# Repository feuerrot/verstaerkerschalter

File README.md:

# Verstärkerschalter

Dieses Projekt dient dazu, auf der Basis von
[vusb](http://www.obdev.at/vusb/) und
[powerswitch](http://www.obdev.at/products/vusb/powerswitch.html) die
Verstärker im [chaosdorf](https://www.chaosdorf.de) zu schalten.

Zudem hat die Platine bereits Bauteile für einen Anschluss per CAN-Bus, was
es später ermöglichen soll, die Platine an das geplante Bussystem im
Chaosdorf anzuschließen.

## Layout und so

### Schaltplan

### Layout

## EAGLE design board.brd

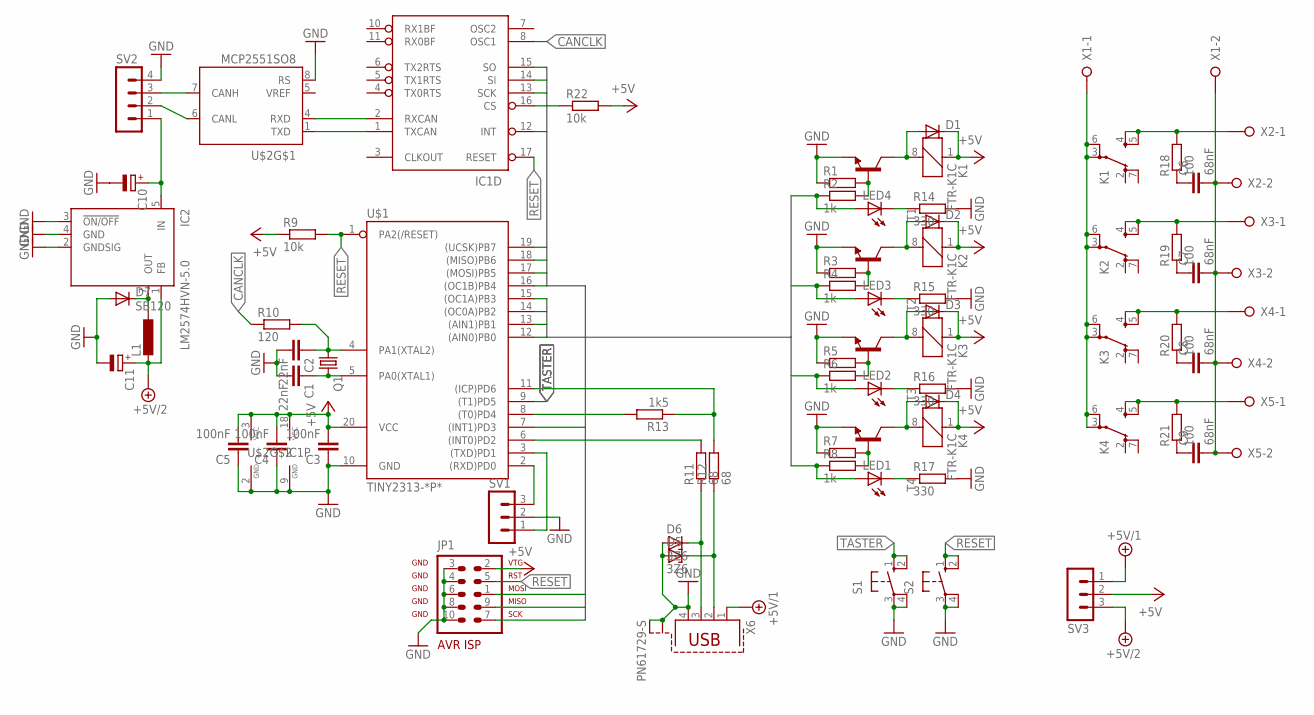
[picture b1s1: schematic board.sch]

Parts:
C1, C2: 22nF; C0805
C3, C4, C5: 100nF; C0805
C6, C7, C8, C9: 68nF; C150-084X183
C10, C11: CPOL-EUD; PANASONIC_D
D1, D2, D3, D4: DIODE-DO-214AC; DO-214AC
D5, D6: 3Z6; SMB
D7: SB120; DO41-10
IC1: MCP2515SO; SO-18W
IC2: LM2574HVN-5.0; DIL08
JP1: AVR-ISP-10
K1, K2, K3, K4: FTR-K1C
L1: L-EUPIS2816; PIS2816
LED1, LED2, LED3, LED4: LED5MM
Q1: CRYSTALHC49U70; HC49U70
R1, R3, R5, R7: R-EU_M0805; M0805
R2, R4, R6, R8: 1k; M0805
R9, R22: 10k; M0805
R10: 120; M0805
R11, R12: 68; M0805
R13: 1k5; M0805
R14, R15, R16, R17: 330; M0805
R18, R19, R20, R21: 100; P0613/15
S1, S2: 10-XX; B3F-10XX
SV1, SV3: MA03-1
SV2: MA04-1
T1, T2, T3, T4: -NPN-SOT23-EBC; SOT23-EBC
U$1: TINY2313-*P*; DIL20
U$2: MCP2551SO8; SO08
X1, X2, X3, X4, X5: W237-02P; W237-132
X6: PN61729-S

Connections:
+5V: C3.2, C4.2, C5.2, D1.C, D2.C, D3.C, D4.C, IC1.18 (VCC), JP1.2, K1.1, K2.1, K3.1, K4.1, R9.1, R22.2, SV3.2, U$1.20 (VCC), U$2.3 (VCC)
+5V/1: SV3.1, X6.1
+5V/2: C11.+, IC2.1 (FB), L1.2, SV3.3
CANCLK: IC1.8 (OSC1), R10.1
CS: IC1.16 (CS), R22.1, U$1.16 ((OC1B)PB4)
GND: C1.2, C2.2, C3.1, C4.1, C5.1, C10.-, C11.-, D5.A, D6.A, D7.A, IC1.9 (GND), IC2.2 (GNDSIG), IC2.3 (!ON/OFF), IC2.4 (GND), JP1.3, JP1.4, JP1.6, JP1.8, JP1.10, R1.1, R3.1, R5.1, R7.1, R14.2, R15.2, R16.2, R17.2, S1.3, S1.4 (P1), S2.3, S2.4 (P1), SV1.2, SV2.4, T1.E, T2.E, T3.E, T4.E, U$1.10 (GND), U$2.2 (GND), U$2.8 (RS), X6.4, X6.S1, X6.S2
INT: IC1.12 (INT), U$1.7 ((INT1)PD3)
MISO: IC1.15 (SO), JP1.9, U$1.18 ((MISO)PB6)
MOSI: IC1.14 (SI), JP1.1, U$1.17 ((MOSI)PB5)
unnamed: K1.3 (PA), K1.6 (PB), K2.3 (PA), K2.6 (PB), K3.3 (PA), K3.6 (PB), K4.3 (PA), K4.6 (PB), X1.1
unnamed: C6.2, C7.2, C8.2, C9.2, X1.2, X2.2, X3.2, X4.2, X5.2
unnamed: K1.4 (SA), K1.5 (SB), R18.2, X2.1
unnamed: K2.4 (SA), K2.5 (SB), R19.2, X3.1
unnamed: K3.4 (SA), K3.5 (SB), R20.2, X4.1
unnamed: K4.4 (SA), K4.5 (SB), R21.2, X5.1
unnamed: D1.A, K1.8 (2), T1.C
unnamed: D7.C, IC2.7 (OUT), L1.1
unnamed: D2.A, K2.8 (2), T2.C
unnamed: R1.2, R2.2, T1.B
unnamed: D3.A, K3.8 (2), T3.C
unnamed: R5.2, R6.2, T3.B
unnamed: D4.A, K4.8 (2), T4.C
unnamed: R7.2, R8.2, T4.B
unnamed: C2.1, Q1.1, R10.2, U$1.4 (PA1(XTAL2))
unnamed: C1.1, Q1.2, U$1.5 (PA0(XTAL1))
unnamed: IC1.2 (RXCAN), U$2.4 (RXD)
unnamed: IC1.1 (TXCAN), U$2.1 (TXD)
unnamed: LED4.K (C), R14.1
unnamed: R11.2, U$1.6 ((INT0)PD2)
unnamed: D6.C, R11.1, X6.3
unnamed: D5.C, R12.1, X6.2
unnamed: LED3.K (C), R15.1
unnamed: R12.2, R13.1, U$1.11 ((ICP)PD6)
unnamed: SV1.1, U$1.3 ((TXD)PD1)
unnamed: SV1.3, U$1.2 ((RXD)PD0)
unnamed: LED2.K (C), R16.1
unnamed: LED1.K (C), R17.1
unnamed: R13.2, U$1.8 ((T0)PD4)
unnamed: C6.1, R18.1
unnamed: C9.1, R21.1
unnamed: C8.1, R20.1
unnamed: C7.1, R19.1
unnamed: SV2.3, U$2.7 (CANH)
unnamed: SV2.2, U$2.6 (CANL)
unnamed: R3.2, R4.2, T2.B
unnamed: C10.+, IC2.5 (IN), SV2.1
RELAI0: LED1.A, R8.1, U$1.12 ((AIN0)PB0)
RELAI1: LED2.A, R6.1, U$1.13 ((AIN1)PB1)
RELAI2: LED3.A, R4.1, U$1.14 ((OC0A)PB2)
RELAI3: LED4.A, R2.1, U$1.15 ((OC1A)PB3)
RESET: IC1.17 (RESET), JP1.5, R9.2, S2.1 (S), S2.2 (S1), U$1.1 (PA2(/RESET))
SCK: IC1.13 (SCK), JP1.7, U$1.19 ((UCSK)PB7)
TASTER: S1.1 (S), S1.2 (S1), U$1.9 ((T1)PD5)

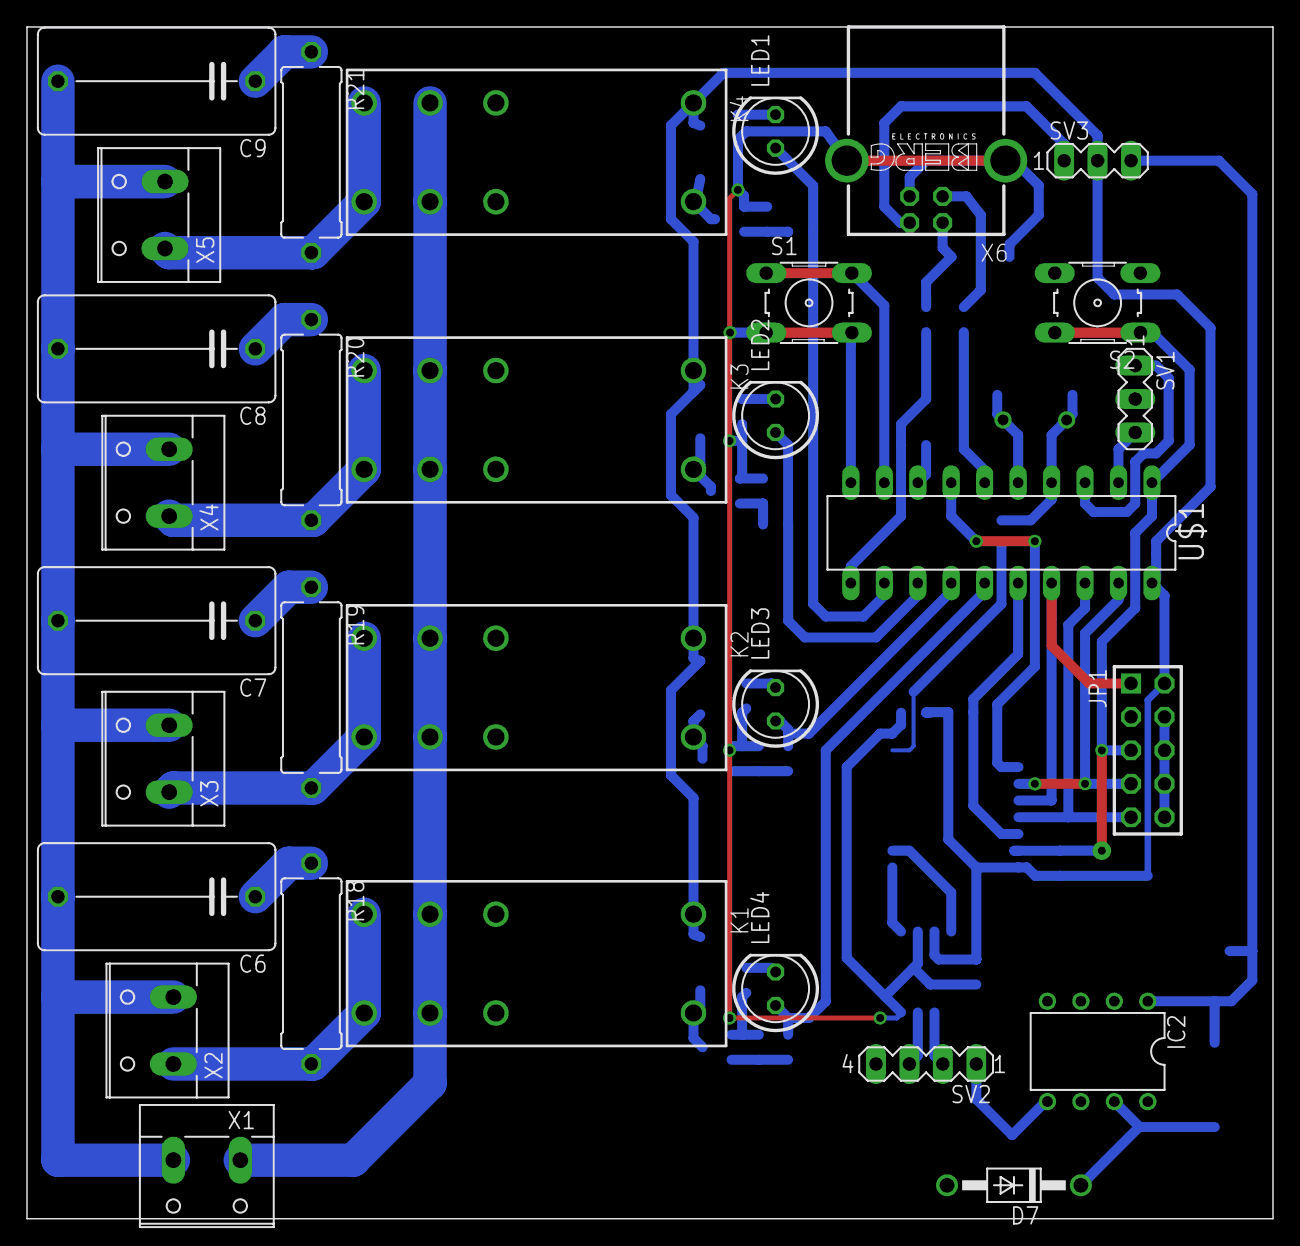
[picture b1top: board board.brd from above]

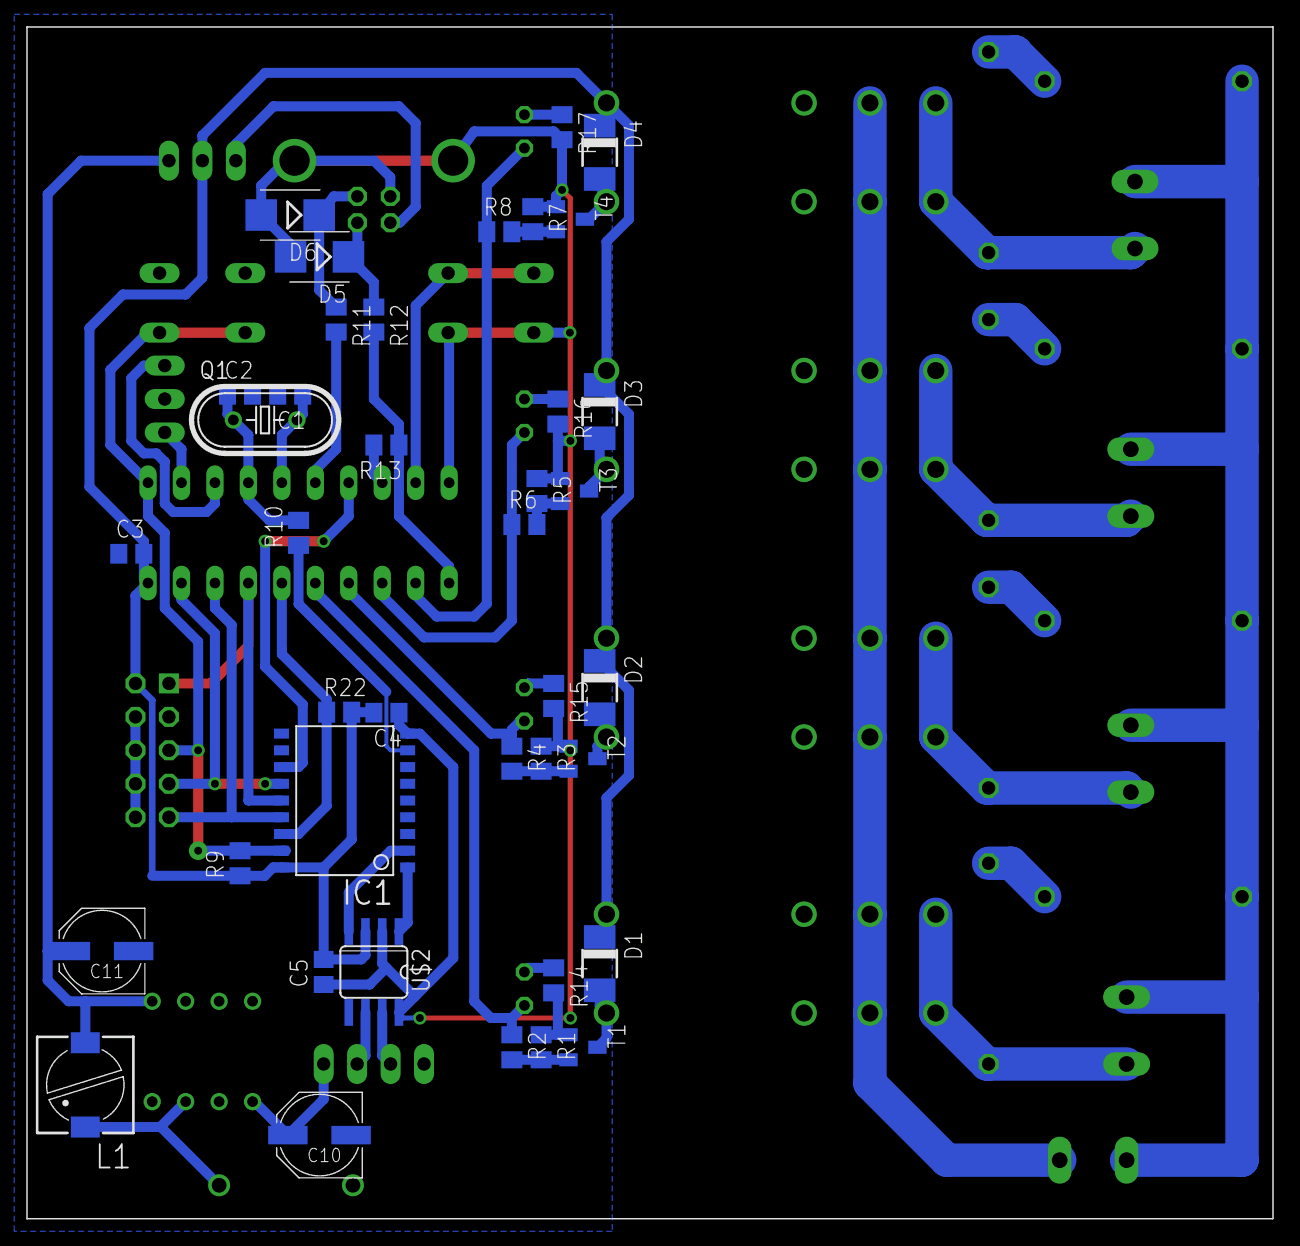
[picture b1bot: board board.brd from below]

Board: 2 copper layers, 94.6 x 90.5 mm, 70 parts (39 on the bottom side), 53 nets.

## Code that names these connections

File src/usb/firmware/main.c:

/* Name: main.c
 * Project: PowerSwitch based on AVR USB driver
 * Author: Christian Starkjohann
 * Creation Date: 2005-01-16
 * Tabsize: 4
 * Copyright: (c) 2005 by OBJECTIVE DEVELOPMENT Software GmbH
 * License: GNU GPL v2 (see License.txt) or proprietary (CommercialLicense.txt)
 * This Revision: $Id$
 */

#include <avr/io.h>
#include <avr/interrupt.h>
#include <avr/pgmspace.h>
#include <avr/eeprom.h>
#include <avr/wdt.h>

#include "usbdrv.h"
#include <util/delay.h>

volatile uint8_t relaistatus;

static void outputByte(){
    PORTB = (PORTB & ~0x0f) | (relaistatus & 0x0f);
}



/* We poll for the timer interrupt instead of declaring an interrupt handler
 * with global interrupts enabled. This saves recursion depth. Our timer does
 * not need high precision and does not run at a high rate anyway.
 */

USB_PUBLIC uchar usbFunctionSetup(uchar data[8]){
usbRequest_t    *rq = (void *)data;
uchar           status = relaistatus;
static uchar    replyBuf[2];

    usbMsgPtr = replyBuf;
    if(rq->bRequest == 0){  /* ECHO */
        replyBuf[0] = rq->wValue.bytes[0];
        replyBuf[1] = rq->wValue.bytes[1];
        return 2;
    }
    if(rq->bRequest == 1){  /* GET_STATUS -> result = 2 bytes */
        replyBuf[0] = status;
        replyBuf[1] = 0;
        return 2;
    }
    if(rq->bRequest == 2 || rq->bRequest == 3){ /* SWITCH_ON or SWITCH_OFF, index = bit number */
        uchar bit = rq->wIndex.bytes[0] & 7;
        uchar mask = 1 << bit;
        uchar needChange, isOn = status & mask;
        if(rq->bRequest == 2){  /* SWITCH_ON */
            status |= mask;
            needChange = !isOn;
        }else{              /* SWITCH_OFF */
            status &= ~mask;
            needChange = isOn;
        }
        relaistatus =  status;
    }
    outputByte();
    return 0;
}

/* allow some inter-device compatibility */
#if !defined TCCR0 && defined TCCR0B
#define TCCR0   TCCR0B
#endif
#if !defined TIFR && defined TIFR0
#define TIFR    TIFR0
#endif

int main(void){

    wdt_enable(WDTO_2S);
    DDRB = ~(1<<PB6);
    PORTB = (1<<PB4);          /* no pullups on USB pins */
    DDRD = ~((1<<PD2) | (1<<PD3) | (1<<PD5));   /* all outputs except PD2 = INT0 */
    PORTD = (1<<PD5);
/* We fake an USB disconnect by pulling D+ and D- to 0 during reset. This is
 * necessary if we had a watchdog reset or brownout reset to notify the host
 * that it should re-enumerate the device. Otherwise the host's and device's
 * concept of the device-ID would be out of sync.
 */
    DDRD = ~USBMASK;    /* set all pins as outputs except USB */
    usbDeviceDisconnect();  /* enforce re-enumeration, do this while interrupts are disabled! */
    _delay_ms(550);
    usbDeviceConnect();
    TCCR0 = 5;          /* set prescaler to 1/1024 */
    usbInit();
    sei();
    for(;;){    /* main event loop */
        wdt_reset();
        usbPoll();
        if(TIFR & (1 << TOV0)){
            TIFR |= 1 << TOV0;  /* clear pending flag */
        }
    }
    return 0;
}

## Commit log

2013-05-23 adding readme, trying markdown
2013-05-23 adding circuit and board
2013-05-23 polygon auf dem board angepasst, schaltplan angepasst
2013-05-31 Hinzufügen der Firmware für usb
    Die Firmware ist von [Objective Development](http://www.obdev.at/products/vusb/powerswitch.html) und steht unter der GPLv2
2013-05-31 Moving the images to a seperate subdir
2013-05-31 adding eagle.epf because eagle wants this
2013-05-31 fixing the link to the circuit
2013-05-31 Moving usb-firmware in subdirectory of src
2013-05-31 Adding hex-file of the firmware to simplify programming
    No one wants to compile the firmware if they don't have avr-gcc already
2013-05-31 Some subtle layout changes
2013-05-31 fixing the fixing
2013-05-31 moar fixing
2013-05-31 New image of the board
2013-05-31 Adding eagle.epf to .gitignore
    Because eagle wants to save a fuckload of data which is private to this file.
2013-05-31 Update eagle.epf, deleting TMI
2013-06-01 Moving one resistor for USB and the ISP-header
2013-06-01 The image of the board has changed
2013-06-02 Adding choice of powersupply, enhancing supply of the tiny, board is a touch larger
2013-06-03 Adding crappy support for a step-down voltage regulator
    Well, there should be a different package for the LM2574…
2013-06-03 New parts => new images
2013-06-03 Fixing paths of images to fit to branch
2013-06-07 relative link in readme
